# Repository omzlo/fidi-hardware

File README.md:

# FIDI 

FIDI is a small development board running Adafruit's CircuitPython, featuring 6 terminal block connectors and a qwiic connector, designed for fast prototyping. It runs on the ATSAMD21 microcontroller, a 32-bit Arm Cortex M0+ clocked at 48Mhz, as found on many popular Arduino-compatible boards.

For more info, see https://www.omzlo.com/fidi

# Acknowledgement 

This design borrows largely from SERPENTE, by Arturo182 (https://github.com/arturo182/serpente_hw).

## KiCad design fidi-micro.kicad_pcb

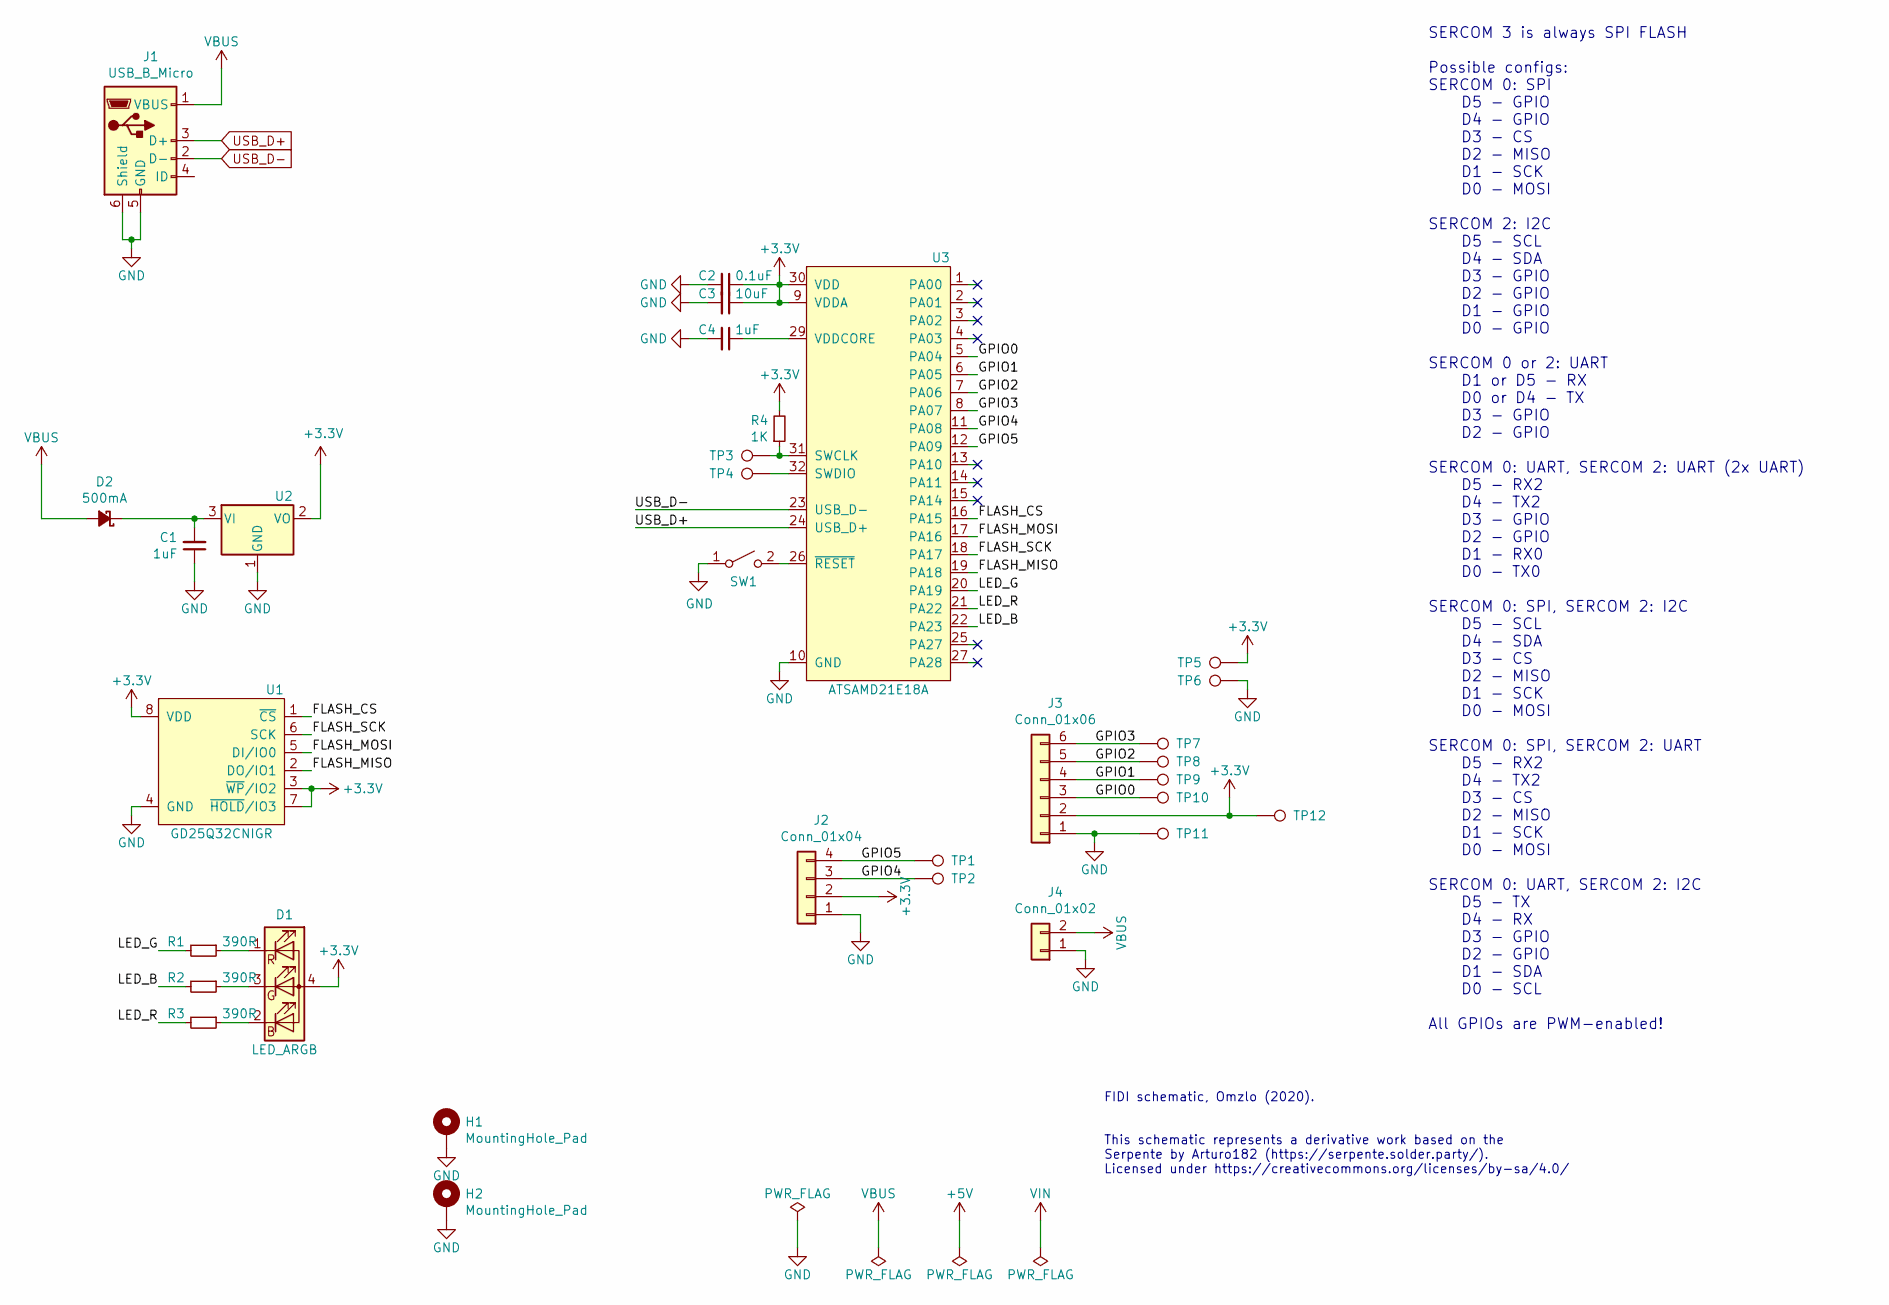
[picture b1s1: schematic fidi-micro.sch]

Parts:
C1, C4: 1uF; C_0603_1608Metric
C2: 0.1uF; C_0603_1608Metric
C3: 10uF; C_0805_2012Metric
D1: LED_ARGB; LED_Cree-PLCC4_2x2mm_CW
D2: 500mA; D_SOD-323_HandSoldering
H1, H2: MountingHole_Pad; MountingHole_2.7mm_M2.5_DIN965_Pad
J1: USB_B_Micro; USB_Micro-B_LCSC_C40951
J2: Conn_01x04; JST_SH_SM04B-SRSS-TB_1x04-1MP_P1.00mm_Horizontal
J3: Conn_01x06; TerminalBlock_4Ucon_1x06_P3.50mm_Horizontal
J4: Conn_01x02; PinHeader_1x02_P2.54mm_Vertical
R1, R2, R3: 390R; R_0603_1608Metric
R4: 1K; R_0603_1608Metric
SW1: SW_RESET; SW_SPST_B3U-1000P
TP1, TP2, TP4, TP7, TP8, TP9, TP10, TP11, TP12: TP_SWDIO; TestPoint_Pad_D1.0mm
TP3: TP_SWCLK; TestPoint_Pad_D1.0mm
TP5: TP_VDD; TestPoint_Pad_D1.0mm
TP6: TP_GND; TestPoint_Pad_D1.0mm
U1: GD25Q32CNIGR; USON-8_3x4mm_P0.8mm
U2: MCP1700-3302E_SOT23; SOT-23
U3: ATSAMD21E18A; QFN-32-1EP_5x5mm_P0.5mm_EP3.6x3.6mm

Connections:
+3V3: C2.1, C3.1, D1.4 (A), J2.2, J3.2, R4.2, TP5.1, TP12.1, U1.3 (~WP~/IO2), U1.7 (~HOLD~/IO3), U1.8 (VDD), U2.2 (VO), U3.9 (VDDA), U3.30 (VDD)
/FLASH_CS: U1.1 (~CS~), U3.16 (PA15)
/FLASH_MISO: U1.2 (DO/IO1), U3.19 (PA18)
/FLASH_MOSI: U1.5 (DI/IO0), U3.17 (PA16)
/FLASH_SCK: U1.6 (SCK), U3.18 (PA17)
/GPIO0: J3.3, TP10.1, U3.5 (PA04)
/GPIO1: J3.4, TP9.1, U3.6 (PA05)
/GPIO2: J3.5, TP8.1, U3.7 (PA06)
/GPIO3: J3.6, TP7.1, U3.8 (PA07)
/GPIO4: J2.3, TP2.1, U3.11 (PA08)
/GPIO5: J2.4, TP1.1, U3.12 (PA09)
/LED_B: R2.2, U3.22 (PA23)
/LED_G: R1.2, U3.20 (PA19)
/LED_R: R3.2, U3.21 (PA22)
GND: C1.1, C2.2, C3.2, C4.2, H1.1, H2.1, J1.5 (GND), J1.6 (Shield), J2.1, J3.1, J4.1, SW1.1 (A), TP6.1, TP11.1, U1.4 (GND), U2.1 (GND), U3.10 (GND), U3.28 (GND)
unnamed: C1.2, D2.1 (K), U2.3 (VI)
unnamed: C4.1, U3.29 (VDDCORE)
unnamed: D1.1 (RK), R1.1
unnamed: D1.2 (BK), R3.1
unnamed: D1.3 (GK), R2.1
unnamed: R4.1, TP3.1, U3.31 (SWCLK)
unnamed: SW1.2 (B), U3.26 (~RESET~)
unnamed: TP4.1, U3.32 (SWDIO)
USB_D+: J1.3 (D+), U3.24 (USB_D+)
USB_D-: J1.2 (D-), U3.23 (USB_D-)
VBUS: D2.2 (A), J1.1 (VBUS), J4.2

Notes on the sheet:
SERCOM 3 is always SPI FLASH Possible configs: SERCOM 0: SPI D5 - GPIO D4 - GPIO D3 - CS D2 - MISO D1 - SCK D0 - MOSI SERCOM 2: I2C D5 - SCL D4 - SDA D3 - GPIO D2 - GPIO D1 - GPIO D0 - GPIO SERCOM 0 or 2: UART D1 or D5 - RX D0 or D4 - TX D3 - GPIO D2 - GPIO SERCOM 0: UART, SERCOM 2: UART (2x UART) 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
This schematic represents a derivative work based on the Serpente by Arturo182 (https://serpente.solder.party/). Licensed under https://creativecommons.org/licenses/by-sa/4.0/
FIDI schematic, Omzlo (2020).

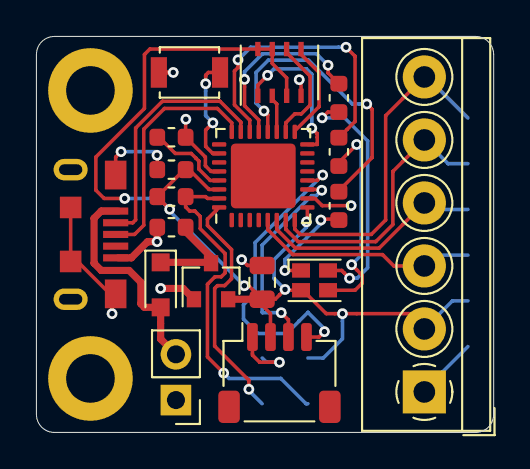
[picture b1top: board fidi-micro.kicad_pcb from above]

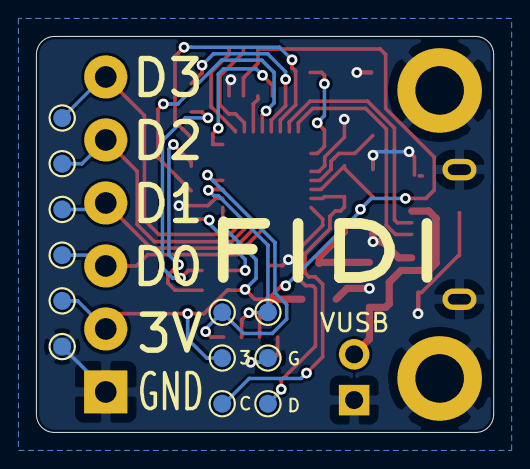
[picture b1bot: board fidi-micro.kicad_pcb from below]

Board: 2 copper layers, 25.4 x 22.0 mm, 32 parts (12 on the bottom side), 26 nets.

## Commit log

2020-05-22 Correct license
